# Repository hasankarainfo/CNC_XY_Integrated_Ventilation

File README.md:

# CNC_XY_Integrated_Ventilation
Diyot lazer uyumlu, bütünleşik havalandırmalı, iki eksen cnc.

Öne Çıkanlar:
1. Çalışması için, ihtiyaç duyduğu tüm materyalleri bütün olarak üzerinde barındırması,
2. Üzerinde bütünleşik bulunan ızgara ile, hava akımı yönlendirilmesi yanısıra, bal peteği ihtiyacının karşılanması,
3. Parça aydınlatma şiddeti, Havalandırma akış hızı, kompresör hava akış hız kontrolcüleri bulunması,
4. Tüm elektronik kontrolcülerin manuel ve ayrık yönetilmesi yanısıra, operasyonla birlikte de otomatik olarak bütünleşik çalışabilmesi,
5. Standart çalışma masası üzerinde, güç soketi ve havalandırma borusu takılmasına takriben kullanıma hazır olması,
6. Üretime uygunluğu ve mekanik dayanımı

Mekanik tasarımlar için FreeCad, Elektronik tasarımlar için ise Kicad, tamamen ücretsiz tasarım programları kullanılarak gerçekleştirildi.

CNC Mekanik boyutlar CNC_XY.FCStd dosyası ana sekmede dd (dynamic data) içerisinde ddSigmaX ve ddSigmaY değişkenleri üzerinden güncellenebilmektedir.
Bu değişkenler tasarımda bulunan x ve y eksenlerinde ki sigma profillerin birebir boylarına eştir. Sigma boylarına bağlı olan tüm parçalar otomatik güncellenecektir.
Bu durumda dikkat edilmesi gereken husus, büküm yapılacak metal parçalarda değişiklik meydana geldiğinge, üretime ilişkin  lazer kesim ve büküm rehberleri,
"./pr_.." dosyaları da ayrıca açılarak el ile güncellenmelidir. 3 boyutlu parçanın lazer kesime ve büküm rehberine uygunluğu için, 
yeniden "unfold" işlemi gerçekleştirilir. Yeniden meydana gelen kesim ve büküm eskiz'leri ilgili parçanın alanına sürüklenir. 
Teknik çizim dosyalarında, view sekmeleri içerisinde, ilişik olduğu eskiz ler, XSource properties üzerinden kesim ve büküm sıralaması ile güncellenir. 
Eski kesim ve büküm eskizleri silinebilir. Bazı durumda teknik çizimde ki ölçü belirteçleri de yeniden belirtilmesi gerekebilmektedir.

ddmove değişkenleri ile lazer hareket ettirilebilir. Sigma boyları ve diğer parametreler değerlendirilerek çalışma alanı otomatik hesaplanır, 
sonuç değerleri ddLimitX ddLimitY parametrelerinde görülür.

Elektriksel bağlantılar, Diyagram takip edilerek gerçekleştirilebilir. Diyagram MSConn board içerisinde tasarlandı, bu sayede kicad projesi üzerinden detaylı incelenebilir.

Üretim için öncelikle BOM dosyası incelenebilir.
Satın alınması gerekli materyallerin, satın alma linkleri ve yaklaşık fiyatlandırmaları Dolar cinsinde görülebilir.
1. sayfada genel toplam ve alt sayfaların sonuç fiyatlandırmaları görülmektedir.
2. sayfada Aygıt kutusu içerisinde kullanılan satın alınması gerekli parçalar görülmektedir.
3. sayfada satın alınması gerekli mekanik parçalar görülmektedir.
4. sayfada Projeye özgün metal parçaların üretilmesi için metal kesim, metal büküm listesi görülmektedir. 
    Dosya isimlerinden, metal kesimde kullanılacak materyalin cinsi ve kalınlığı anlaşılmaktadır.
    İhtiyaç duyulan kesim dosyaları, büküm rehberleri ve diş açma rehberleri "./Mechanic_60x100/Production_.." klasörlerinde bulunabilir.
5. sayfada "Multi Speed Controller and Connections" kartının üretiminde kullanılacak elektronik komponentlerin listesi bulunmaktadır.
    PCB üretiminde ihtiyaç duyulacak gerber dosyası "./HW/MSConn/FabOut_MSConn.zip" bulunabilir. 
    PCB Prototiplemede kullanılmak üzere detaylı MSConn bom listesi "./HW/MSConn/bom/ibom_MSConn.html"bulunabilir.
    Kart üzerinde konnektör pin isimleri anlamları ile birlikte yazmaktadır.

"./Mechanic_60x100/Media/" içerisinde ilk prototip montajına ilişkin fotoğraflar yer almaktadır. İlk prototip montaj esnasında,
görülen eksiklikler doğrultusunda, mekanik ve donanım tasarımlarında, gerekli görülen güncellemeler uygulanmıştır.

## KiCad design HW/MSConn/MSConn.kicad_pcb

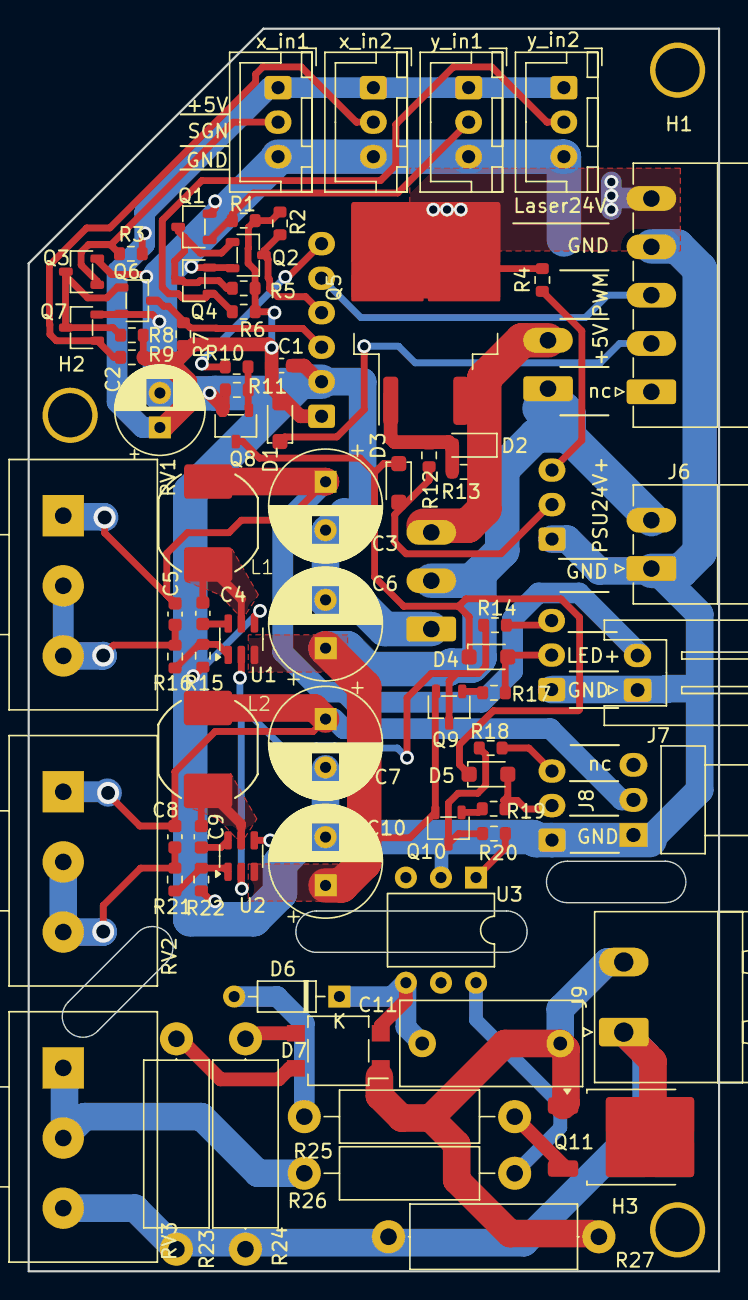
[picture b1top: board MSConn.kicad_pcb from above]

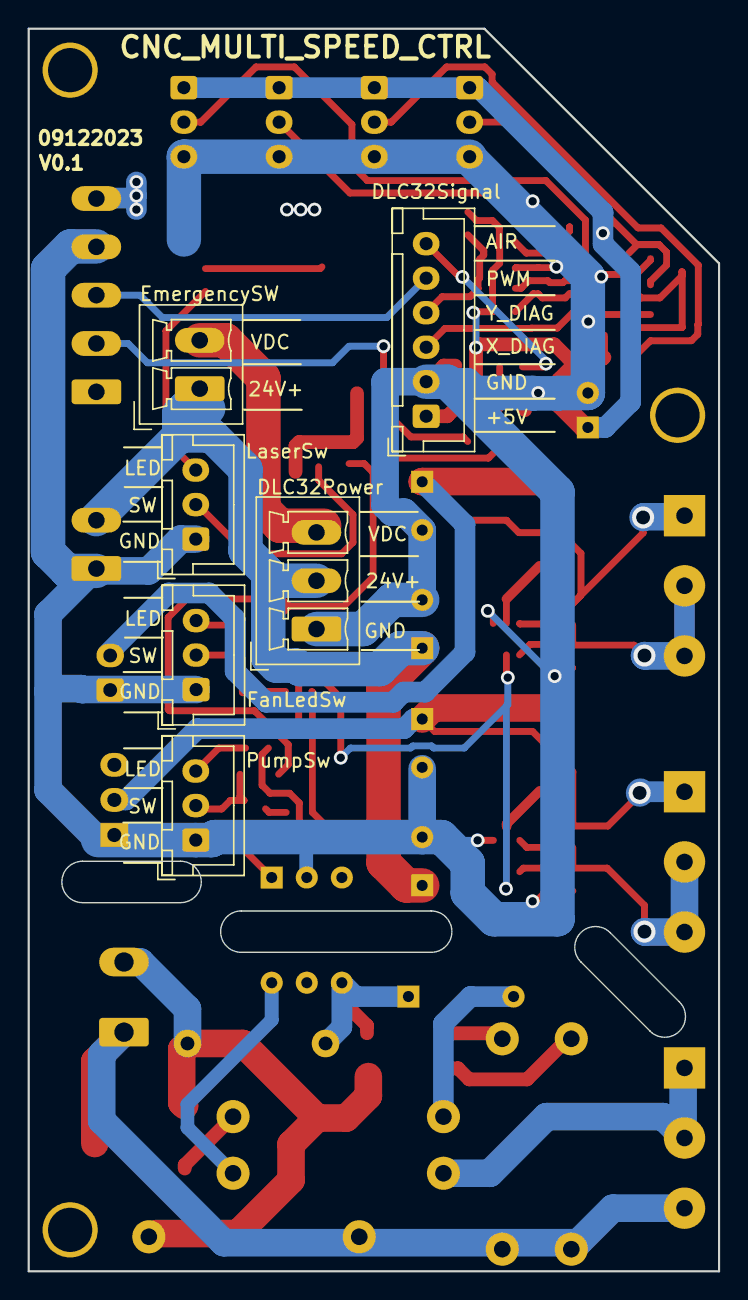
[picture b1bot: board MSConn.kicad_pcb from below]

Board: 2 copper layers, 50.0 x 90.0 mm, 82 parts (6 on the bottom side), 49 nets.

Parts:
C1, C4, C9: 100nF; C_0603_1608Metric
C2: 220uF 25V; CP_Radial_D6.3mm_H11.0mm_P2.50mm
C3, C6, C7, C10: 220uF 35V; CP_Radial_D8.0mm_H12.0mm_P3.50mm
C5, C8: 47pF; C_0603_1608Metric
C11: 100nF 275Vac; C_Rect_L13.0mm_W6.0mm_P10.00mm_FKS3_FKP3_MKS4
D1, D3, D4, D5: 1N4148; D_SOD-123F-s
D2: MM3Z12; D_SOD-323_HandSoldering
D6: DB3; D_DO-35_SOD27_P7.62mm_Horizontal
D7: MB6S; TO-269AA_spec
H1, H2, H3: M3; MountingHole_3.2mm_M3_DIN965_SmallPad
J1: x_in1; JST_XH_B3B-XH-A_1x03_P2.50mm_Vertical
J2: x_in2; JST_XH_B3B-XH-A_1x03_P2.50mm_Vertical
J3: y_in1; JST_XH_B3B-XH-A_1x03_P2.50mm_Vertical
J4: y_in2; JST_XH_B3B-XH-A_1x03_P2.50mm_Vertical
J5: Laser Terminal; PhoenixContact_MC_1,5_5-G-3.5_1x05_P3.50mm_Horizontal
J6: PSU24V+; PhoenixContact_MC_1,5_2-G-3.5_1x02_P3.50mm_Horizontal
J7: LED+; JST_XH_S2B-XH-A_1x02_P2.50mm_Horizontal
J8: FAN+; FanPinHeader_1x03_P2.54mm_Horizontal
J9: Pump220V; PhoenixContact_MSTBA_2,5_2-G-5,08_1x02_P5.08mm_Horizontal
J10: EmergencySW; PhoenixContact_MCV_1,5_2-G-3.5_1x02_P3.50mm_Vertical
J11: DLC32Signal; JST_XH_B6B-XH-A_1x06_P2.50mm_Vertical
J12: LaserSw; JST_XH_B3B-XH-A_1x03_P2.50mm_Vertical
J13: DLC32Power; PhoenixContact_MCV_1,5_3-G-3.5_1x03_P3.50mm_Vertical
J14: FanLedSw; JST_XH_B3B-XH-A_1x03_P2.50mm_Vertical
J15: PumpSw; JST_XH_B3B-XH-A_1x03_P2.50mm_Vertical
L1, L2: 10uH 3.4A; CD75_Inductor
Q1, Q2, Q3, Q4, Q6, Q7, Q8: PJA3440; SOT-23-3-s
Q5: IRF9540N; TO-263-2-S
Q9, Q10: MMBTA92; SOT-23-3-s
Q11: BTA204S-800E; TO-252-2
R1, R2, R3, R5, R6, R7, R8, R9: 10K; R_0603_1608Metric
R4, R10, R12, R14, R18: 4.7K; R_0603_1608Metric
R11, R13, R17, R19: 100K; R_0603_1608Metric
R15: 750R; R_0603_1608Metric
R16: 12K; R_0603_1608Metric
R20: 2K; R_0603_1608Metric
R21: 3.9K; R_0603_1608Metric
R22: 470R; R_0603_1608Metric
R23, R24: 100K; R_Axial_DIN0414_L11.9mm_D4.5mm_P15.24mm_Horizontal
R25: 1K; R_Axial_DIN0411_L9.9mm_D3.6mm_P15.24mm_Horizontal
R26: 270R; R_Axial_DIN0411_L9.9mm_D3.6mm_P15.24mm_Horizontal
R27: 47K; R_Axial_DIN0414_L11.9mm_D4.5mm_P15.24mm_Horizontal
RV1, RV2: 10K; Potentiometer_Alps_RK163_Single_Horizontal
RV3: 500K; Potentiometer_Alps_RK163_Single_Horizontal
U1, U2: AP63300; TSOT-23-6_SlimPad
U3: MOC3063M; DIP-6_W7.62mm

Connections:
+5V: C1.1, C2.1, D1.2 (A), J1.1, J2.1, J3.1, J4.1, J11.1, R1.1, R2.1, R3.1, R5.1, R6.1, R7.1, R8.1, R9.1
+24V: C6.1, C10.1, J6.2, J10.1, J13.2, Q9.2 (E), Q10.2 (E), U1.3 (IN), U2.3 (IN)
/AC1: J9.1, Q11.2 (A2), R23.2, R24.2, R27.2, RV3.3
/FB: R21.2, R22.2, U2.1 (FB)
/FB1: R15.2, R16.2, U1.1 (FB)
/Fan_Drv: C7.1, C8.1, J8.2, L2.2, RV2.1
/Fan_Led_Btn: D4.2 (A), J14.2, R17.1
/Fan_Led_En: Q9.3 (C), R14.2, U1.2 (EN), U2.2 (EN)
/Laser_Btn: D3.2 (A), J12.2, R12.1
/Laser_Power: J5.5, Q5.2 (S), R4.2
/Led_Drv: C3.1, C5.1, J7.2, L1.2, RV1.1
/Pump_Btn: D5.2 (A), J15.2, R19.1
/Pump_En: Q10.3 (C), R18.2, R20.2
/SGN_AIR: J11.6, R10.2
/SGN_PWM: J5.3, J11.5
/X_DIAG: J11.3, Q6.3 (D), R7.2
/Y_DIAG: J11.4, Q2.3 (D), R2.2
/x_in1: J1.2, Q3.1 (G), R3.2
/x_in2: J2.2, Q7.1 (G), R9.2
/y_in1: J3.2, Q1.1 (G), R1.2
/y_in2: J4.2, Q4.1 (G), R6.2
/~AC1: C11.2, D7.1, J9.2, Q11.1 (A1), R27.1
/~Air: D3.1 (K), D4.1 (K), D5.1 (K), Q8.3 (D)
GND: C1.2, C2.2, C3.2, C6.2, C7.2, C10.2, J1.3, J2.3, J3.3, J4.3, J5.4, J6.1, J7.1, J8.1, J11.2, J12.1, J13.1, J14.1, J15.1, Q1.2 (S), Q2.2 (S), Q3.2 (S), Q4.2 (S), Q6.2 (S), Q7.2 (S), Q8.2 (S), R11.2, R15.1, R22.1, U1.4 (GND), U2.4 (GND), U3.2
unnamed: C5.2, R16.1, RV1.2, RV1.3
unnamed: C8.2, R21.1, RV2.2, RV2.3
unnamed: D1.1 (K), J5.2
unnamed: D2.2 (A), Q5.1 (G), R12.2, R13.2
unnamed: D6.2 (A), R25.1
unnamed: C11.1, D6.1 (K), D7.2, U3.4
unnamed: D7.3 (+), R24.1
unnamed: D7.4 (-), R23.1
unnamed: J12.3, R4.1
unnamed: J14.3, R14.1
unnamed: J15.3, R18.1
unnamed: Q1.3 (D), Q2.1 (G), Q4.3 (D), R5.2
unnamed: Q3.3 (D), Q6.1 (G), Q7.3 (D), R8.2
unnamed: Q8.1 (G), R10.1, R11.1
unnamed: Q9.1 (B), R17.2
unnamed: Q10.1 (B), R19.2
unnamed: Q11.3 (G), R25.2
unnamed: R20.1, U3.1
unnamed: R26.1, RV3.1, RV3.2
unnamed: R26.2, U3.6
unnamed: C4.2, U1.6 (BST)
unnamed: C4.1, L1.1, U1.5 (SW)
unnamed: C9.2, U2.6 (BST)
unnamed: C9.1, L2.1, U2.5 (SW)
VDC: D2.1 (K), J10.2, J13.3, Q5.3 (D), R13.1

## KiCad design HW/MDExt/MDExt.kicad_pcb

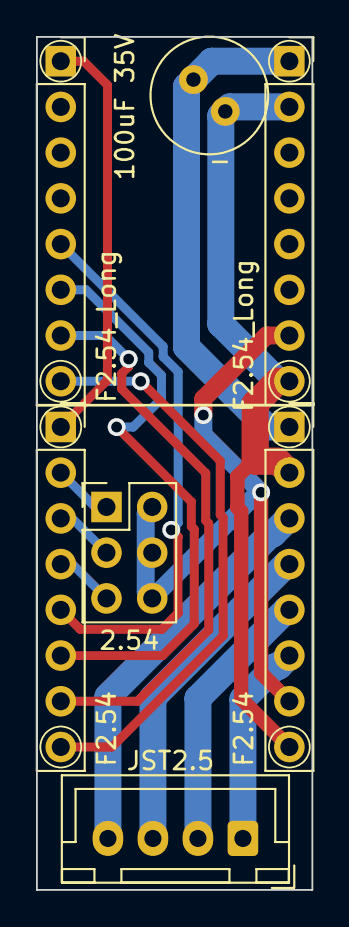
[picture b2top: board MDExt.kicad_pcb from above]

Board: 2 copper layers, 15.3 x 47.4 mm, 9 parts (0 on the bottom side), 15 nets.

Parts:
C1: 100uF 35V; C_Radial_D6.3mm_H11.0mm_P2.50mm
J1, J2: F2.54; PinSocket_1x08_P2.54mm_Vertical
J3: 2.54; PinHeader_2x03_P2.54mm_Vertical
J4, J5: F2.54_Long; PinSocket_1x08_P2.54mm_Vertical_Long
J6: JST2.5; JST_XH_B4B-XH-A_1x04_P2.50mm_Vertical
SYM1, SYM2: SYM_TMC2209_3D; Module_TMC2209_3D

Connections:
+5V: J2.7, J3.2, J3.4, J3.6, J5.7
+12V: C1.1, J2.1, J5.1
/MDriverExtendY/DIR: J1.8, J4.8
/MDriverExtendY/EN: J1.1, J4.1
/MDriverExtendY/RST: J1.5, J4.5
/MDriverExtendY/SLP: J1.6, J4.6
/MDriverExtendY/STP: J1.7, J4.7
GND: C1.2, J2.2, J2.8, J5.2, J5.8
unnamed: J1.2, J3.1
unnamed: J1.3, J3.3
unnamed: J1.4, J3.5
unnamed: J2.3, J6.4
unnamed: J2.4, J6.3
unnamed: J2.5, J6.2
unnamed: J2.6, J6.1

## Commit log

2024-03-12 Readme Update.
2024-03-12 Readme Update
2024-03-14 .gitignore update
